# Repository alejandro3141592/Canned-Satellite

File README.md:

# Canned-Satellite

This repository contains the work made for the Iberoamerican Contest of Canned Satellite 2023, which consisted of the development of a telemetry system oriented to the instrumentation of variables in a free fall from 400 meters.

The system consisted of a cylinder with a diameter of 10 cm and a height of 22 cm and had the necessary components to sense the altitude, the pressure, the temperature, the satellite yaw, pitch, and roll, among others. In addition, the satellite is designed to be dropped at a height of 400 meters, and then at 250 meters deploy an autogyro system that is in charge of decreasing the speed fall of the satellite.

In order to make the satellite work, I developed all the electronic systems, in charge of sensing all the needed variables, and decoupling the secondary charge of the system.

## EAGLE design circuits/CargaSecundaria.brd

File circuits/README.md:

In this folder, I present an electronic circuit design in Proteus that corresponds to the primary and secondary charge of the Canned Satellite.

The first circuit is in charge of sensing all the variables required by the contest committee, including the temperature, altitude, pressure, pitch, yaw and roll, and so on. 

The second circuit is in charge of decoupling the secondary stage of the satellite and sending messages to the primary stage.

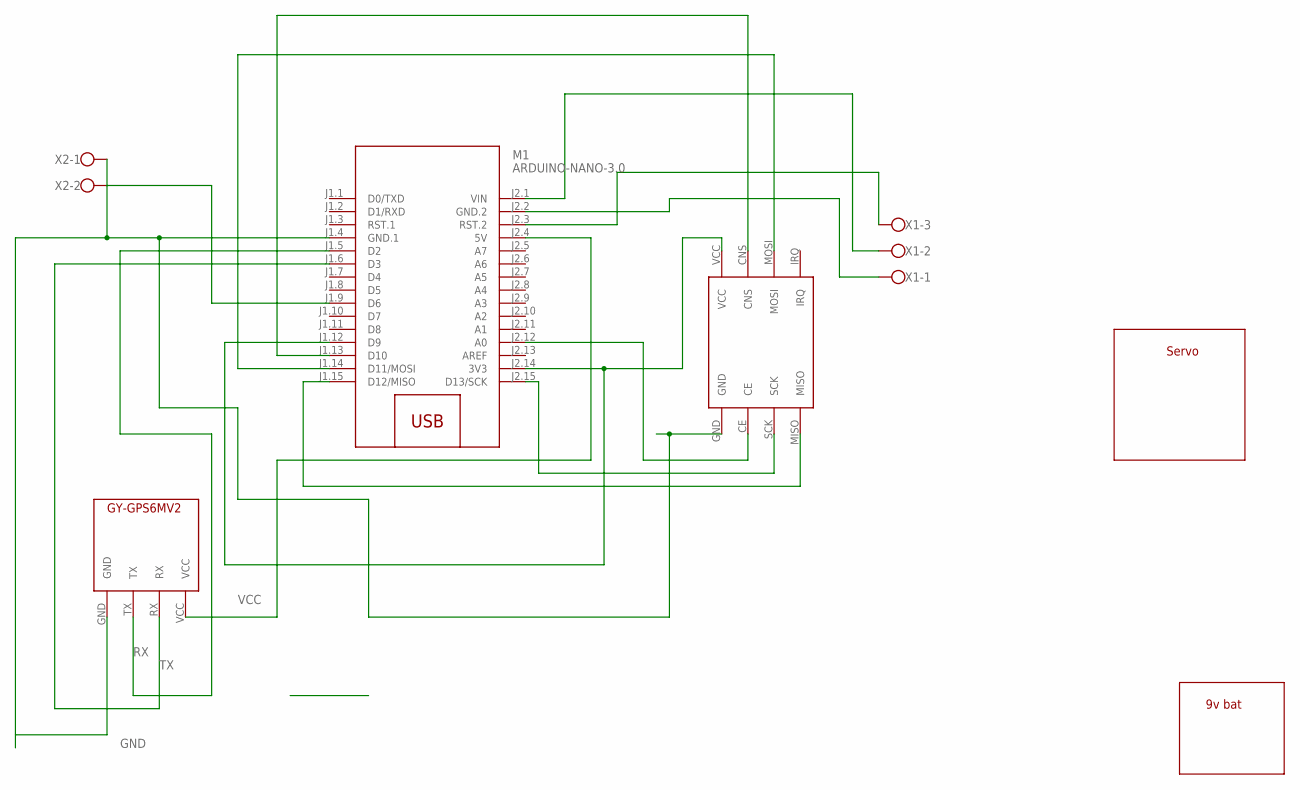
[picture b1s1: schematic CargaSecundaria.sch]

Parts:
M1: ARDUINO-NANO-3.0
U$2: SERVO_DEVICE; SERVO_FOOTPRINT
U$3: NRF24L01_DEVICE; NRF24L01_FOOTPRINT
U$4: 9VBAT_DEVICE; 9V_FOOTRPRINT
U$5: GY-GPS6M_VUPDOWMNLIB; GY-GPS6M_FOOTPRINT_UPSIDEDOWN
X1: W237-103
X2: W237-102

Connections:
GND: M1.J1.4 (GND.1), U$3.GND, U$5.GND, X2.1
unnamed: M1.J1.13 (D10), U$3.CNS
unnamed: M1.J2.3 (RST.2), X1.3
unnamed: M1.J1.9 (D6), X2.2
unnamed: M1.J1.12 (D9), M1.J2.14 (3V3), U$3.VCC
unnamed: M1.J2.2 (GND.2), X1.1
unnamed: M1.J2.1 (VIN), X1.2
unnamed: M1.J2.15 (D13/SCK), U$3.SCK
unnamed: M1.J2.12 (A0), U$3.CE
unnamed: M1.J1.15 (D12/MISO), U$3.MISO
unnamed: M1.J1.14 (D11/MOSI), U$3.MOSI
RX: M1.J1.5 (D2), U$5.TX
TX: M1.J1.6 (D3), U$5.RX
VCC: M1.J2.4 (5V), U$5.VCC

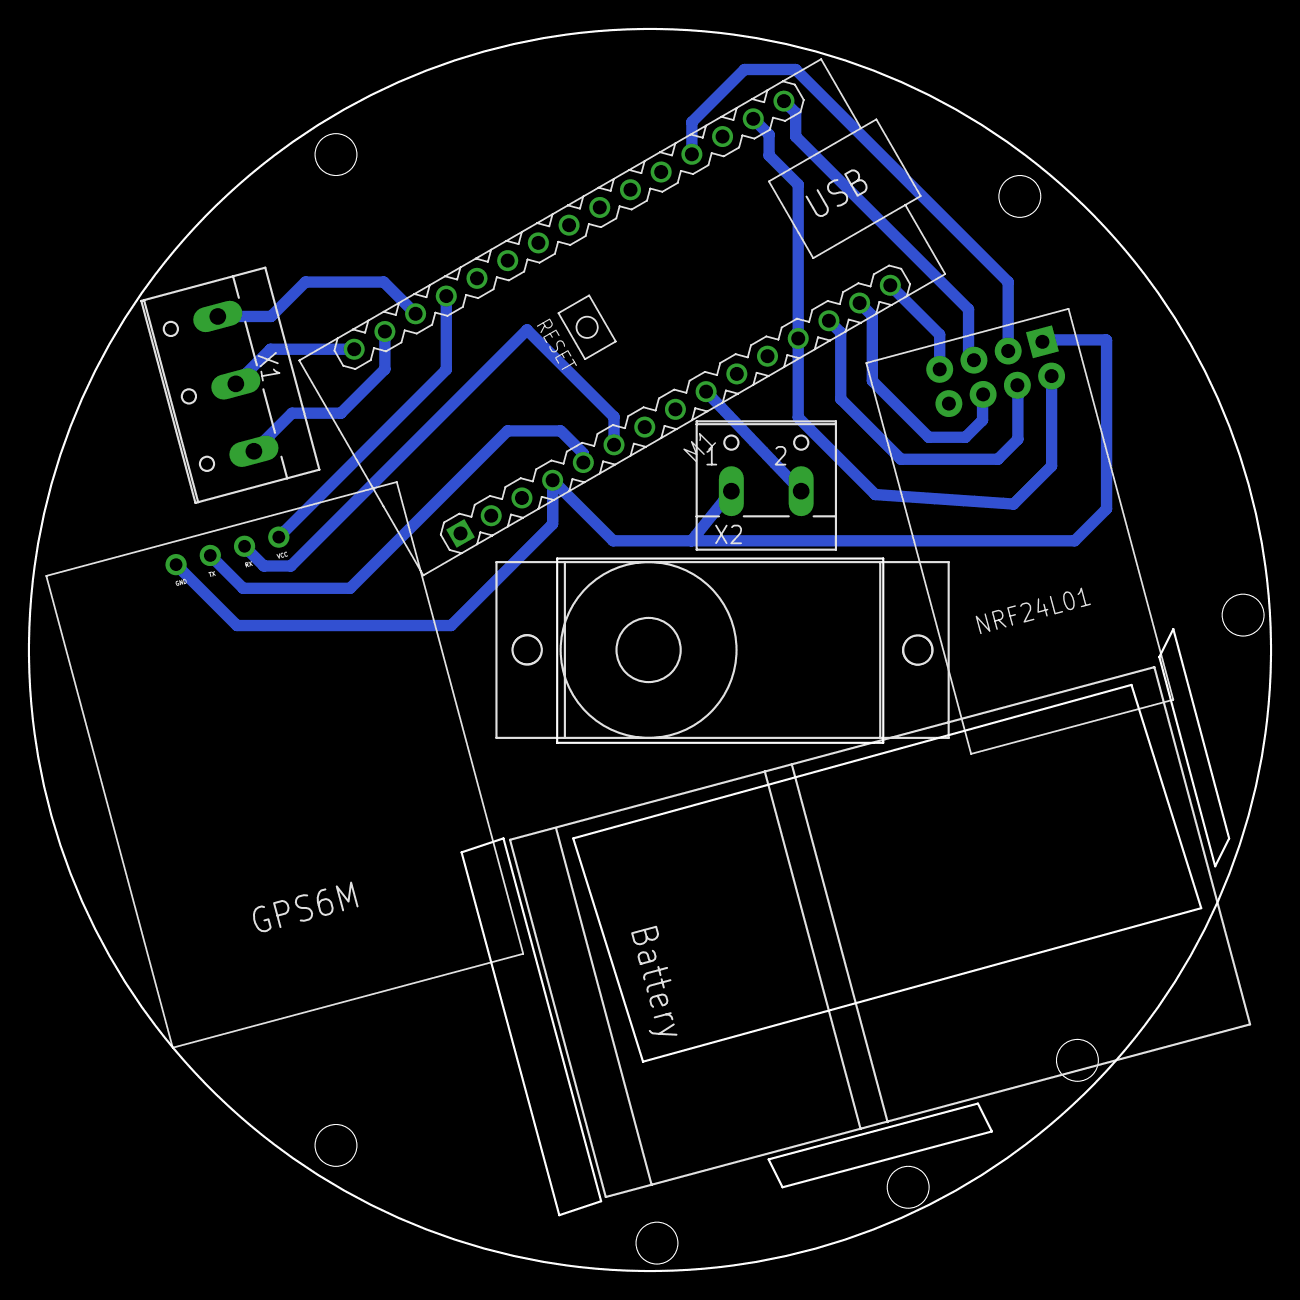
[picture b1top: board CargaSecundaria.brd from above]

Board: 2 copper layers, 89.0 x 89.0 mm, 7 parts (0 on the bottom side), 14 nets.

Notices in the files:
parts and their libraries:
diy-modules: Released under the Creative Commons Attribution 4.0 International License: http://creativecommons.org/licenses/by/4.0
